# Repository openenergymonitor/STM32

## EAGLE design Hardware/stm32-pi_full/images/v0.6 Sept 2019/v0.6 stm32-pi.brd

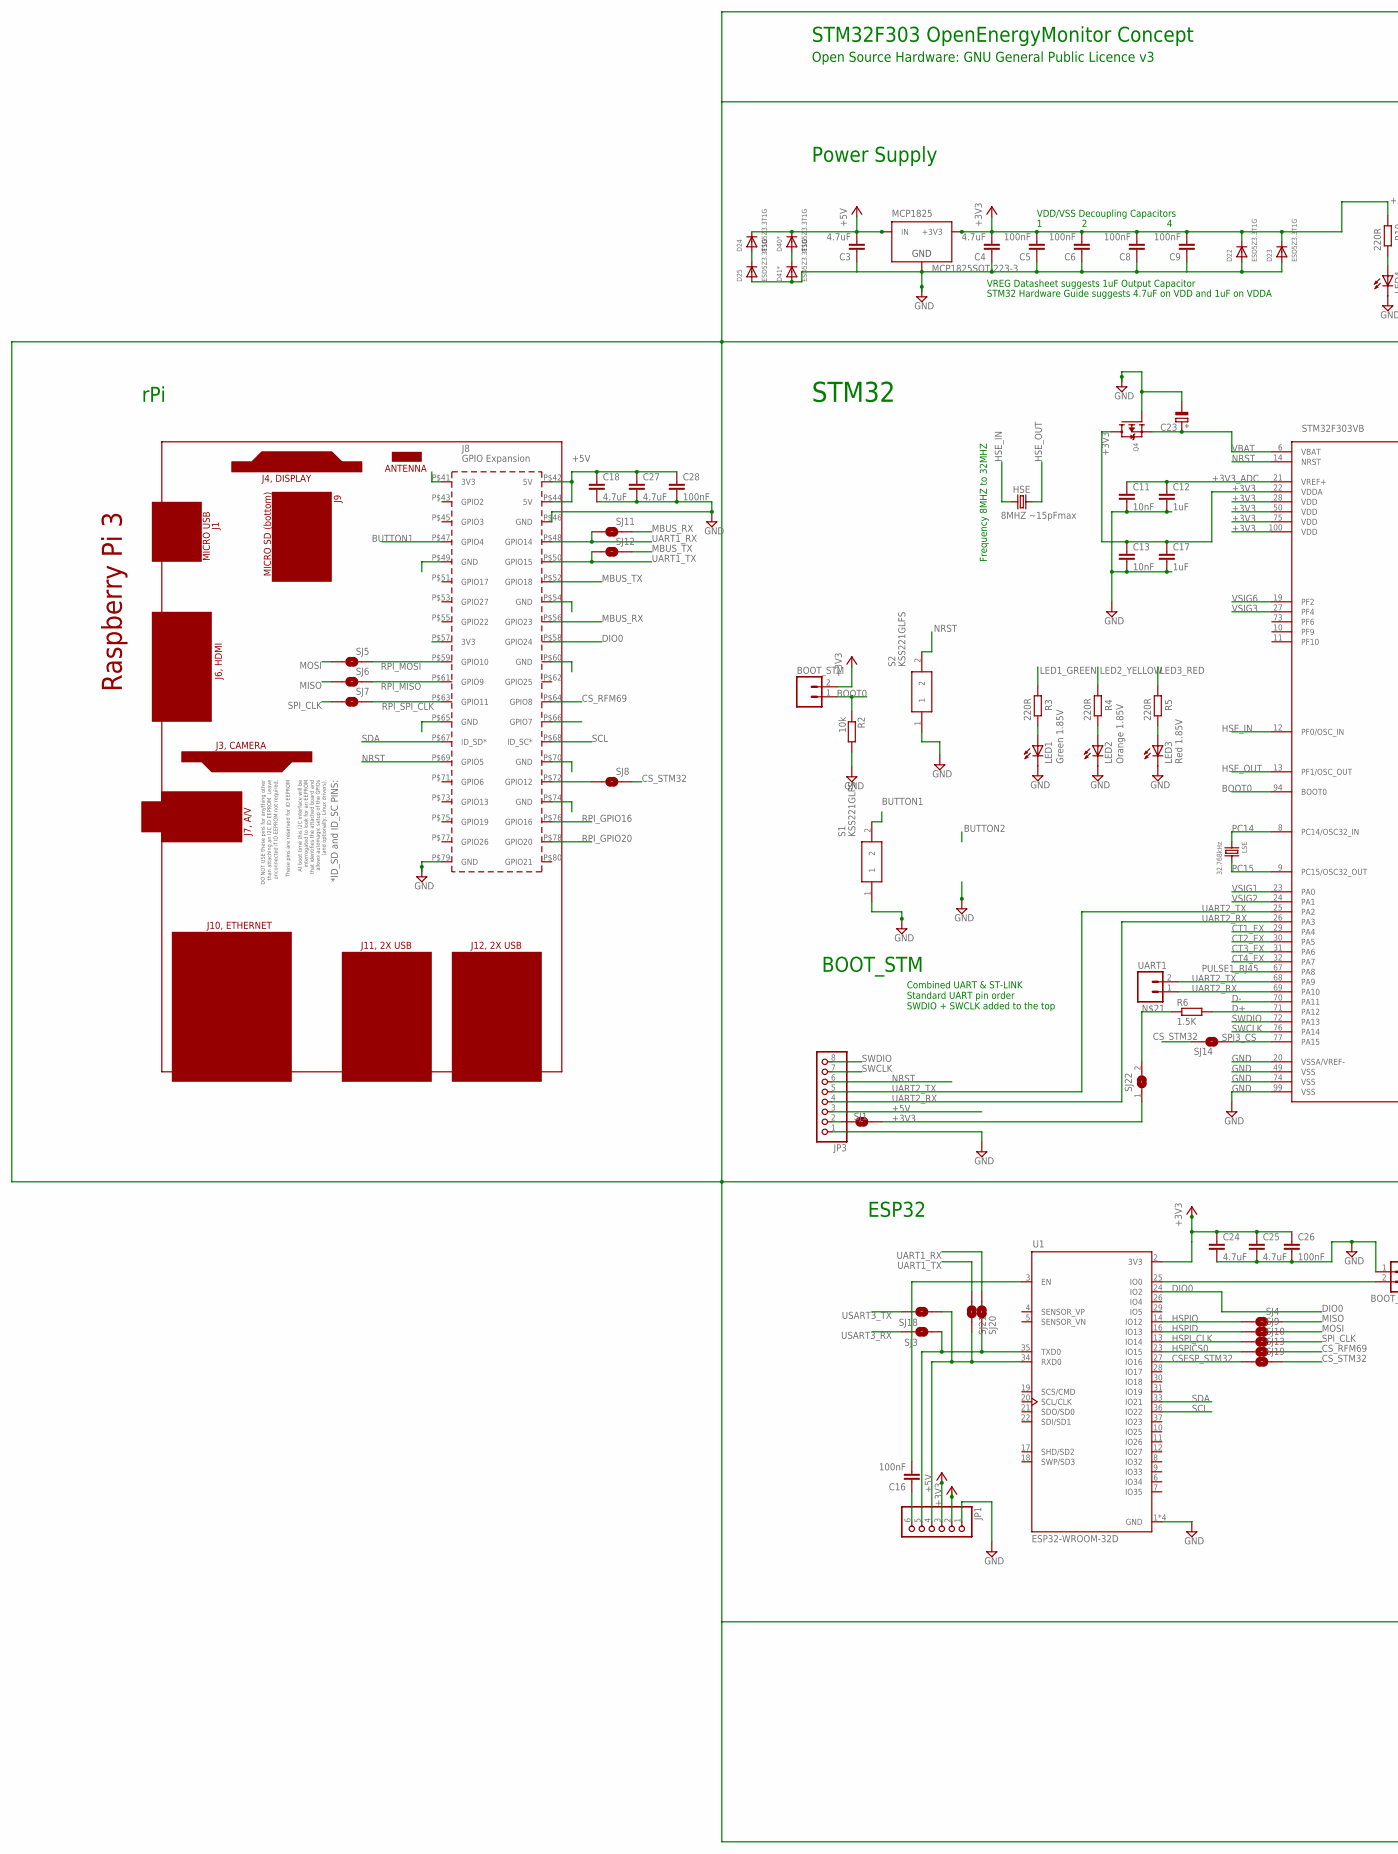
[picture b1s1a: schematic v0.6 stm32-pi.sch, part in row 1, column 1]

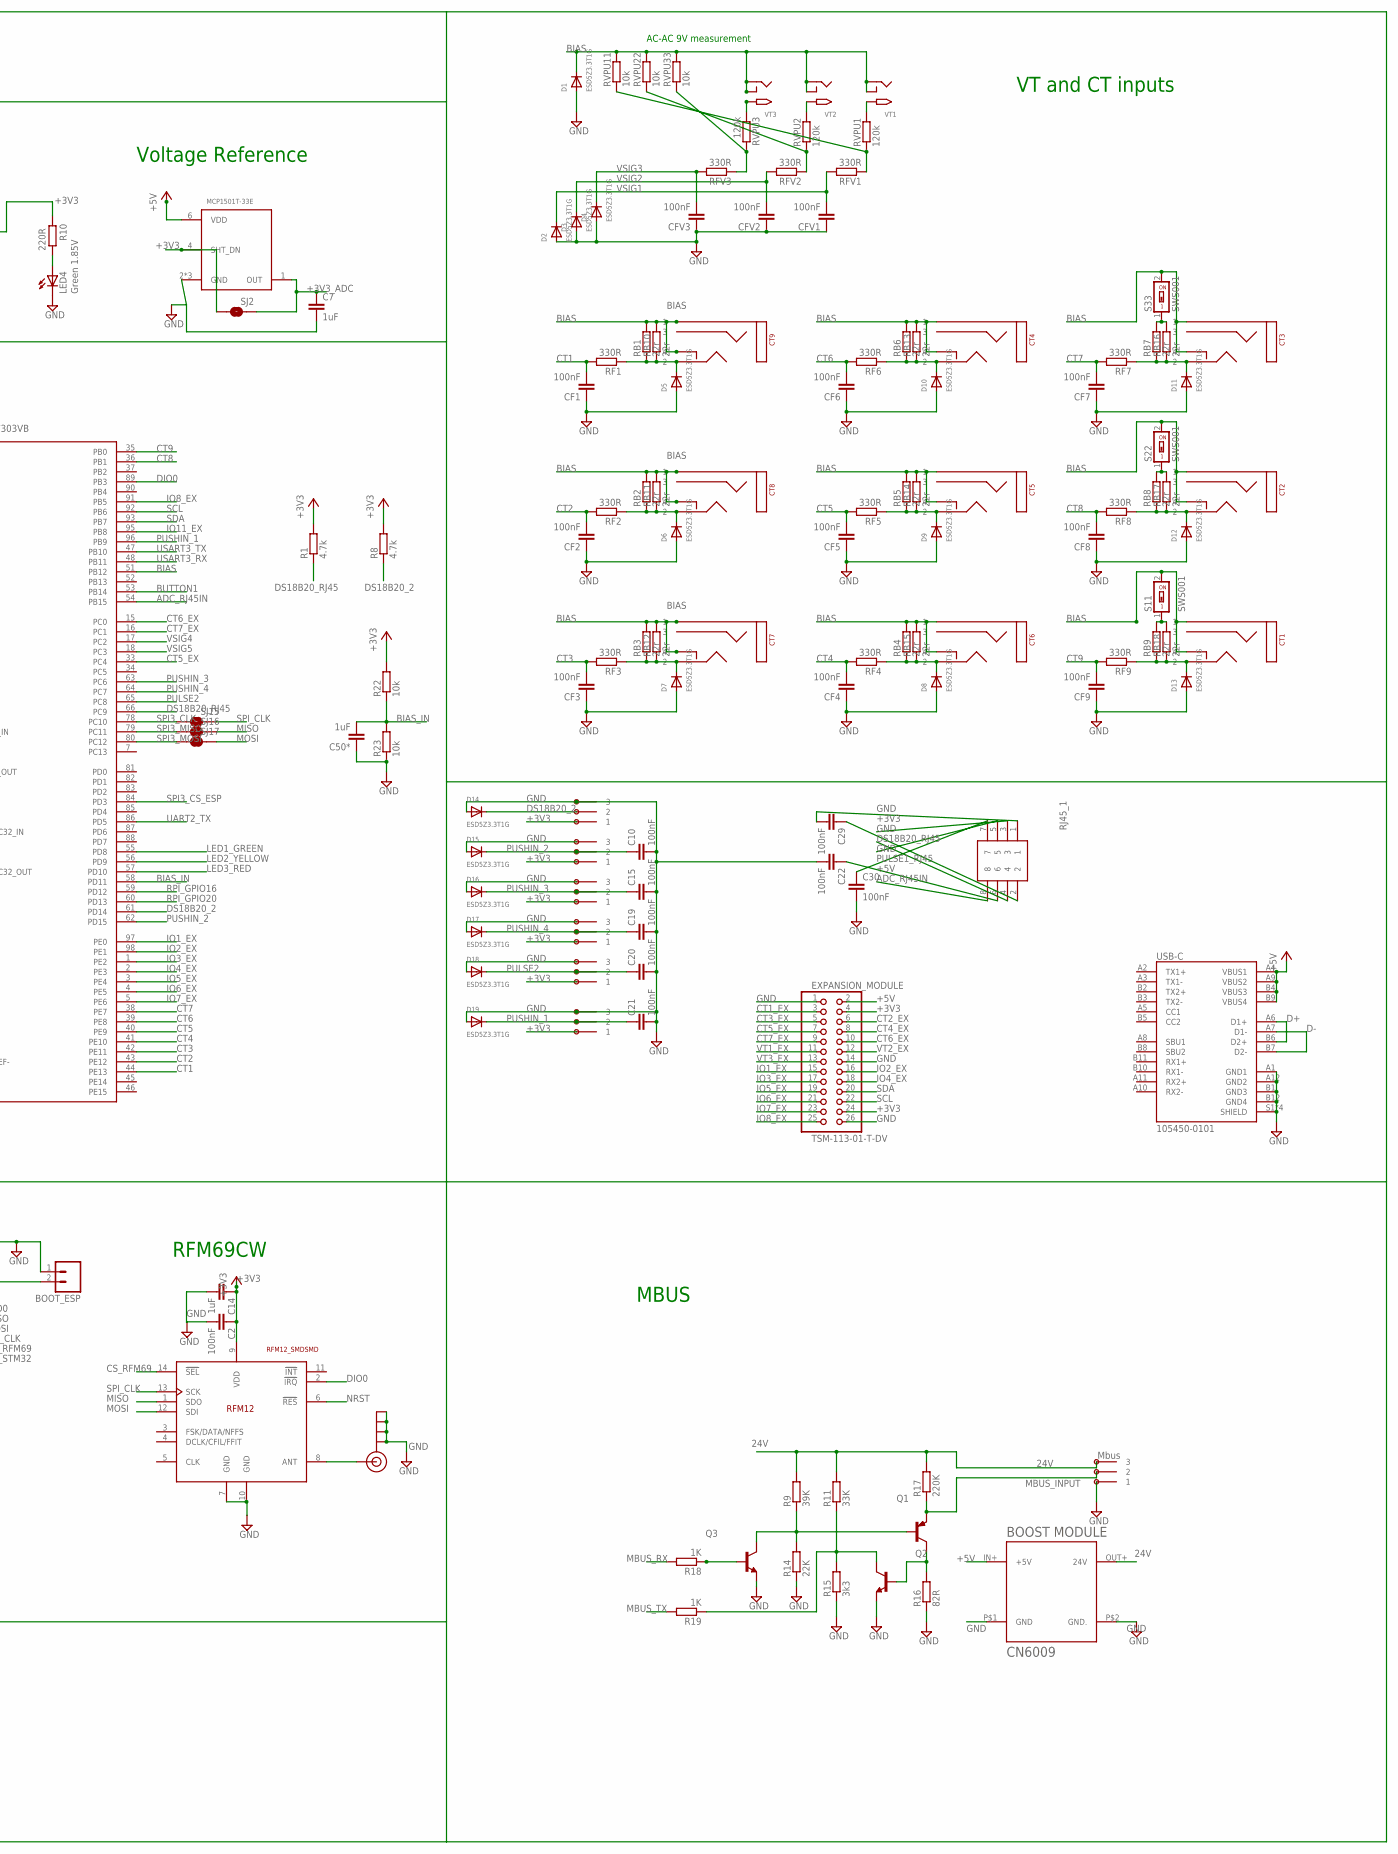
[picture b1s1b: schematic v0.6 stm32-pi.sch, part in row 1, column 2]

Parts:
3POLE_1, 3POLE_2, 3POLE_3, 3POLE_4, 3POLE_5, 3POLE_6, 3POLE_7: OMNIMATE_LSF_3COMBICON_SMT_3; OMNIMATE_LSF_3_SMT
BOOT_ESP: M02PTH; 1X02
BOOT_STM: M02PTH; 1X02
C2, C5, C6, C8, C9, C10, C15, C16, C19, C20, C21, C22, C26, C28, C29, C30: 100nF; C0603
C3, C4, C18, C24, C25, C27: 4.7uF; C0805
C7, C12, C14, C17: 1uF; C0805
C11, C13: 10nF; C0603
C23: CPOL-EU153CLV-1010; 153CLV-1010
C50*: 1uF; C0603
CF1, CF2, CF3, CF4, CF5, CF6, CF7, CF8, CF9: 100nF; C0603
CFV1, CFV2, CFV3: 100nF; C0603
CT1, CT2, CT3, CT4, CT5, CT6, CT7, CT8, CT9: STEREO_SMD; STEREO_SMT
D1, D2, D3, D4, D5, D6, D7, D8, D9, D10, D11, D12, D13, D14, D15, D16, D17, D18, D19, D22, D23, D24, D25, D40*, D41*: ESD5Z3.3T1G; SOD-523
EXPANSION_MODULE: TSM-113-01-T-DV; 2X13_SMT
HSE: 8MHZ ~15pFmax; CTS406
J$1: SMA_EDGE; SMA-EDGE
JP1: PINHD-1X61X06_SMT; 1X06_SMT
JP3: PINHD-1X81X08_SMT; 1X08_SMT
LED1, LED4: Green 1.85V; CHIP-LED0805
LED2: Orange 1.85V; CHIP-LED0805
LED3: Red 1.85V; CHIP-LED0805
LSE: 32.768kHz; CRYSTAL_8X3.8
MCP1825: MCP1825SOT-223-3; SOT-223
PCB2: RPI3YA; RPI3MIRROR2
Q1: MMBT3906; SOT23
Q2, Q3: MMBT3904; SOT23
Q4: MOSFET-P; SOT23-R
R1, R8: 4.7k; R0603
R2, R22, R23: 10k; R0603
R3, R4, R5, R10: 220R; R0603
R6: 1.5K; R0603
R9: 39K; R0603
R11: 33K; R0603
R14: 22K; R0603
R15: 3k3; R0603
R16: 82R; R0603
R17: 220K; R0603
R18, R19: 1K; R0603
RB1, RB2, RB3, RB4, RB5, RB6, RB7, RB8, RB9: 22r; R0603
RB10, RB11, RB12, RB13, RB14, RB15, RB16, RB17, RB18: 22r; 0207/7
RF1, RF2, RF3, RF4, RF5, RF6, RF7, RF8, RF9: 330R; R0603
RFM69HCW: RFM12_SMDSMD; RFM12
RFV1, RFV2, RFV3: 330R; R0603
RJ45_1: 95501-6889; 955016889
RVPU1, RVPU2, RVPU3: 120k; R0603
RVPU11, RVPU22, RVPU33: 10k; R0603
S1, S2: KSS221GLFS; KSS
S11, S22, S33: SWS001; SMS-001
SJ1, SJ2, SJ3, SJ4, SJ5, SJ6, SJ7, SJ8, SJ9, SJ10, SJ11, SJ12, SJ13, SJ14, SJ15, SJ16, SJ17, SJ18, SJ19, SJ20, SJ21: SOLDERJUMPERNO; SJ_2S-NO
SJ22: SJ-CONCON; SJ-CON
STM32F303VB: STM32F303XB; TQFP100
U1: ESP32-WROOM-32D; MODULE_ESP32-WROOM-32D
U$2: BOOST_MODULE; BOOST
UART1: M02PTH; 1X02
USB-C: 105450-0101; MOLEX_105450-0101
VREF_3V3: MCP1501T-33E; SOT95P280X145-6N
VT1, VT2, VT3: 2.1MMJACKSMT; DCJACK_2MM_SMT

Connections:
24V: 3POLE_7.P$3 (3), R9.2, R11.2, R17.2, U$2.OUT+ (24V)
+3V3: 3POLE_1.P$1 (1), 3POLE_2.P$1 (1), 3POLE_3.P$1 (1), 3POLE_4.P$1 (1), 3POLE_5.P$1 (1), 3POLE_6.P$1 (1), BOOT_STM.2, C2.1, C4.2, C5.2, C6.2, C8.2, C9.2, C13.1, C14.1, C17.1, C24.1, C25.1, C26.1, C29.1, D22.K (C), D23.K (C), EXPANSION_MODULE.4, EXPANSION_MODULE.24, JP1.2, MCP1825.3 (+3V3), Q4.3 (D), R1.2, R8.2, R10.2, R22.2, RFM69HCW.9 (VDD), RJ45_1.2, SJ1.2, SJ2.1, SJ22.1, STM32F303VB.22 (VDDA), STM32F303VB.28 (VDD), STM32F303VB.50 (VDD), STM32F303VB.75 (VDD), STM32F303VB.100 (VDD), U1.2 (3V3), VREF_3V3.4 (SHT_DN)
+3V3_ADC: C7.1, C11.1, C12.1, SJ2.2, STM32F303VB.21 (VREF+), VREF_3V3.1 (OUT)
+5V: C3.2, C18.1, C27.1, C28.1, C30.1, D24.K (C), D40*.K (C), EXPANSION_MODULE.2, JP1.3, JP3.3, MCP1825.1 (IN), PCB2.P$42 (5V), PCB2.P$44 (5V), RJ45_1.7, U$2.IN+ (+5V), USB-C.A4 (VBUS1), USB-C.A9 (VBUS2), USB-C.B4 (VBUS3), USB-C.B9 (VBUS4), VREF_3V3.6 (VDD)
AC1: RVPU1.2, VT1.PWR2 (TIP)
AC2: RVPU2.2, VT2.PWR2 (TIP)
AC3: RVPU3.1, VT3.PWR2 (TIP)
ADC0: RFV3.1, RVPU3.2, RVPU33.1
ADC_RJ45IN: RJ45_1.8, STM32F303VB.54 (PB15)
BIAS: CT1.P$1 (1), CT1.P$4 (4), CT2.P$1 (1), CT2.P$4 (4), CT3.P$1 (1), CT3.P$4 (4), CT4.P$1 (1), CT4.P$4 (4), CT5.P$1 (1), CT5.P$4 (4), CT6.P$1 (1), CT6.P$4 (4), CT7.P$1 (1), CT7.P$4 (4), CT8.P$1 (1), CT8.P$4 (4), CT9.P$1 (1), CT9.P$4 (4), D1.K (C), RB1.2, RB2.2, RB3.2, RB4.2, RB5.2, RB6.2, RB10.2, RB11.2, RB12.2, RB13.2, RB14.2, RB15.2, RVPU11.2, RVPU22.2, RVPU33.2, S11.2, S22.2, S33.2, STM32F303VB.51 (PB12), VT1.GND (RING), VT1.GNDBREAK (RING_SW), VT2.GND (RING), VT2.GNDBREAK (RING_SW), VT3.GND (RING), VT3.GNDBREAK (RING_SW)
BIAS_IN: C50*.2, R22.1, R23.2, STM32F303VB.58 (PD11)
BOOT0: BOOT_STM.1, R2.1, STM32F303VB.94 (BOOT0)
BUTTON1: PCB2.P$47 (GPIO4), S1.2, STM32F303VB.53 (PB14)
CSESP_STM32: SJ19.1, U1.27 (IO16)
CS_RFM69: PCB2.P$64 (GPIO8), RFM69HCW.14 (!SEL), SJ13.2
CS_STM32: SJ8.2, SJ14.1, SJ19.2
CT1: CF1.2, RF1.2, STM32F303VB.44 (PE13)
CT1_EX: EXPANSION_MODULE.3, STM32F303VB.29 (PA4)
CT2: CF2.2, RF2.2, STM32F303VB.43 (PE12)
CT2_EX: EXPANSION_MODULE.6, STM32F303VB.30 (PA5)
CT3: CF3.2, RF3.2, STM32F303VB.42 (PE11)
CT3_EX: EXPANSION_MODULE.5, STM32F303VB.31 (PA6)
CT4: CF4.2, RF4.2, STM32F303VB.41 (PE10)
CT4_EX: EXPANSION_MODULE.8, STM32F303VB.32 (PA7)
CT5: CF5.2, RF5.2, STM32F303VB.40 (PE9)
CT5_EX: EXPANSION_MODULE.7, STM32F303VB.33 (PC4)
CT6: CF6.2, RF6.2, STM32F303VB.39 (PE8)
CT6_EX: EXPANSION_MODULE.10, STM32F303VB.15 (PC0)
CT7: CF7.2, RF7.2, STM32F303VB.38 (PE7)
CT7_EX: EXPANSION_MODULE.9, STM32F303VB.16 (PC1)
CT8: CF8.2, RF8.2, STM32F303VB.36 (PB1)
CT9: CF9.2, RF9.2, STM32F303VB.35 (PB0)
D+: R6.2, STM32F303VB.71 (PA12), USB-C.A6 (D1+), USB-C.B6 (D2+)
D-: STM32F303VB.70 (PA11), USB-C.A7 (D1-), USB-C.B7 (D2-)
DIO0: PCB2.P$58 (GPIO24), RFM69HCW.2 (!IRQ), STM32F303VB.89 (PB3), U1.24 (IO2)
DS18B20_2: 3POLE_1.P$2 (2), D14.K (C), R8.1, STM32F303VB.61 (PD14)
DS18B20_RJ45: R1.1, RJ45_1.4, STM32F303VB.66 (PC9)
GND: 3POLE_1.P$3 (3), 3POLE_2.P$3 (3), 3POLE_3.P$3 (3), 3POLE_4.P$3 (3), 3POLE_5.P$3 (3), 3POLE_6.P$3 (3), 3POLE_7.P$1 (1), BOOT_ESP.1, C2.2, C3.1, C4.1, C5.1, C6.1, C7.2, C8.1, C9.1, C10.2, C11.2, C12.2, C13.2, C14.2, C15.2, C17.2, C18.2, C19.2, C20.2, C21.2, C22.2, C23.-, C24.2, C25.2, C26.2, C27.2, C28.2, C29.2, C30.2, C50*.1, CF1.1, CF2.1, CF3.1, CF4.1, CF5.1, CF6.1, CF7.1, CF8.1, CF9.1, CFV1.1, CFV2.1, CFV3.1, D1.A, D2.A, D3.A, D4.A, D5.A, D6.A, D7.A, D8.A, D9.A, D10.A, D11.A, D12.A, D13.A, D14.A, D15.A, D16.A, D17.A, D18.A, D19.A, D22.A, D23.A, D25.A, D41*.A, EXPANSION_MODULE.1, EXPANSION_MODULE.14, EXPANSION_MODULE.26, J$1.GND@0 (GND), J$1.GND@1 (GND), J$1.GND@2 (GND), J$1.GND@3 (GND), JP1.1, JP3.1, LED1.C, LED2.C, LED3.C, LED4.C, MCP1825.2 (GND), MCP1825.4 (GND), PCB2.P$46 (GND), PCB2.P$49 (GND), PCB2.P$54 (GND), PCB2.P$60 (GND), PCB2.P$65 (GND), PCB2.P$70 (GND), PCB2.P$74 (GND), PCB2.P$79 (GND), Q2.2 (E), Q3.2 (E), Q4.1 (G), R2.2, R14.1, R15.1, R16.1, R23.1, RFM69HCW.7 (GND), RFM69HCW.10 (GND), RJ45_1.1, RJ45_1.3, RJ45_1.5, S1.1, S2.1, STM32F303VB.20 (VSSA/VREF-), STM32F303VB.49 (VSS), STM32F303VB.74 (VSS), STM32F303VB.99 (VSS), U1.1 (GND), U1.15 (GND), U1.38 (GND), U1.39 (GND), U$2.P$1 (GND), U$2.P$2 (GND.), USB-C.A1 (GND1), USB-C.A12 (GND2), USB-C.B1 (GND3), USB-C.B12 (GND4), USB-C.S1 (SHIELD), USB-C.S2 (SHIELD), USB-C.S3 (SHIELD), USB-C.S4 (SHIELD), VREF_3V3.2 (GND), VREF_3V3.3 (GND), VREF_3V3.5 (GND)
HSE_IN: HSE.1, STM32F303VB.12 (PF0/OSC_IN)
HSE_OUT: HSE.3 (2), STM32F303VB.13 (PF1/OSC_OUT)
HSPICS0: SJ13.1, U1.23 (IO15)
HSPID: SJ9.1, U1.16 (IO13)
HSPIQ: SJ4.1, U1.14 (IO12)
HSPI_CLK: SJ10.1, U1.13 (IO14)
IO1_EX: EXPANSION_MODULE.15, STM32F303VB.97 (PE0)
IO2_EX: EXPANSION_MODULE.16, STM32F303VB.98 (PE1)
IO3_EX: EXPANSION_MODULE.17, STM32F303VB.1 (PE2)
IO4_EX: EXPANSION_MODULE.18, STM32F303VB.2 (PE3)
IO5_EX: EXPANSION_MODULE.19, STM32F303VB.3 (PE4)
IO6_EX: EXPANSION_MODULE.21, STM32F303VB.4 (PE5)
IO7_EX: EXPANSION_MODULE.23, STM32F303VB.5 (PE6)
IO8_EX: EXPANSION_MODULE.25, STM32F303VB.91 (PB5)
IO11_EX: STM32F303VB.95 (PB8)
LED1_GREEN: R3.2, STM32F303VB.55 (PD8)
LED2_YELLOW: R4.2, STM32F303VB.56 (PD9)
LED3_RED: R5.2, STM32F303VB.57 (PD10)
MBUS_INPUT: 3POLE_7.P$2 (2), Q1.2 (E), R17.1
MBUS_RX: PCB2.P$56 (GPIO23), R18.2, SJ11.2
MBUS_TX: PCB2.P$52 (GPIO18), R19.2, SJ12.2
MISO: RFM69HCW.1 (SDO), SJ4.2, SJ6.1, SJ16.2
MOSI: RFM69HCW.12 (SDI), SJ5.1, SJ9.2, SJ17.2
unnamed: JP3.2, SJ1.1
unnamed: CT9.P$2 (2), D5.K (C), RB1.1, RB10.1, RF1.1
unnamed: LED2.A, R4.1
unnamed: LED3.A, R5.1
unnamed: JP1.5, SJ3.1, SJ20.2, U1.35 (TXD0)
unnamed: CT8.P$2 (2), D6.K (C), RB2.1, RB11.1, RF2.1
unnamed: LED4.A, R10.1
unnamed: CT7.P$2 (2), D7.K (C), RB3.1, RB12.1, RF3.1
unnamed: JP1.4, SJ18.1, SJ21.2, U1.34 (RXD0)
unnamed: STM32F303VB.68 (PA9), UART1.2
unnamed: C16.1, JP1.6
unnamed: C16.2, U1.3 (EN)
unnamed: PCB2.P$72 (GPIO12), SJ8.1
unnamed: BOOT_ESP.2, U1.25 (IO0)
unnamed: D24.A, D25.K (C)
unnamed: D40*.A, D41*.K (C)
unnamed: J$1.SIG (SIGNAL), RFM69HCW.8 (ANT)
unnamed: R6.1, SJ22.2
unnamed: STM32F303VB.69 (PA10), UART1.1
unnamed: RB9.2, RB18.2, S11.1
unnamed: RB8.2, RB17.2, S22.1
unnamed: RB7.2, RB16.2, S33.1
unnamed: Q1.3 (C), Q2.1 (B), R16.2
unnamed: Q1.1 (B), Q3.3 (C), R9.1, R14.2
unnamed: Q2.3 (C), R11.1, R15.2, R19.1
unnamed: Q3.1 (B), R18.1
unnamed: RFV2.1, RVPU2.1, RVPU22.1
unnamed: RFV1.1, RVPU1.1, RVPU11.1
unnamed: CT6.P$2 (2), D8.K (C), RB4.1, RB15.1, RF4.1
unnamed: CT5.P$2 (2), D9.K (C), RB5.1, RB14.1, RF5.1
unnamed: CT4.P$2 (2), D10.K (C), RB6.1, RB13.1, RF6.1
unnamed: LED1.A, R3.1
unnamed: CT3.P$2 (2), D11.K (C), RB7.1, RB16.1, RF7.1
unnamed: CT2.P$2 (2), D12.K (C), RB8.1, RB17.1, RF8.1
unnamed: CT1.P$2 (2), D13.K (C), RB9.1, RB18.1, RF9.1
NRST: JP3.6, PCB2.P$69 (GPIO5), RFM69HCW.6 (!RES), S2.2, STM32F303VB.14 (NRST)
PC14: LSE.P$1 (1), STM32F303VB.8 (PC14/OSC32_IN)
PC15: LSE.P$4 (2), STM32F303VB.9 (PC15/OSC32_OUT)
PULSE1_RJ45: C22.1, RJ45_1.6, STM32F303VB.67 (PA8)
PULSE2: 3POLE_5.P$2 (2), C20.1, D18.K (C), STM32F303VB.65 (PC8)
PUSHIN_1: 3POLE_6.P$2 (2), C21.1, D19.K (C), STM32F303VB.96 (PB9)
PUSHIN_2: 3POLE_2.P$2 (2), C10.1, D15.K (C), STM32F303VB.62 (PD15)
PUSHIN_3: 3POLE_3.P$2 (2), C15.1, D16.K (C), STM32F303VB.63 (PC6)
PUSHIN_4: 3POLE_4.P$2 (2), C19.1, D17.K (C), STM32F303VB.64 (PC7)
RPI_GPIO16: PCB2.P$76 (GPIO16), STM32F303VB.59 (PD12)
RPI_GPIO20: PCB2.P$78 (GPIO20), STM32F303VB.60 (PD13)
RPI_MISO: PCB2.P$61 (GPIO9), SJ6.2
RPI_MOSI: PCB2.P$59 (GPIO10), SJ5.2
RPI_SPI_CLK: PCB2.P$63 (GPIO11), SJ7.2
SCL: EXPANSION_MODULE.22, PCB2.P$68 (ID_SC*), STM32F303VB.92 (PB6), U1.36 (IO22)
SDA: EXPANSION_MODULE.20, PCB2.P$67 (ID_SD*), STM32F303VB.93 (PB7), U1.33 (IO21)
SPI3_CLK: SJ15.1, STM32F303VB.78 (PC10)
SPI3_CS: SJ14.2, STM32F303VB.77 (PA15)
SPI3_CS_ESP: STM32F303VB.84 (PD3)
SPI3_MISO: SJ16.1, STM32F303VB.79 (PC11)
SPI3_MOSI: SJ17.1, STM32F303VB.80 (PC12)
SPI_CLK: RFM69HCW.13 (SCK), SJ7.1, SJ10.2, SJ15.2
SWCLK: JP3.7, STM32F303VB.76 (PA14)
SWDIO: JP3.8, STM32F303VB.72 (PA13)
UART1_RX: PCB2.P$48 (GPIO14), SJ11.1, SJ20.1
UART1_TX: PCB2.P$50 (GPIO15), SJ12.1, SJ21.1
UART2_RX: JP3.4, STM32F303VB.26 (PA3)
UART2_TX: JP3.5, STM32F303VB.25 (PA2), STM32F303VB.86 (PD5)
USART3_RX: SJ3.2, STM32F303VB.48 (PB11)
USART3_TX: SJ18.2, STM32F303VB.47 (PB10)
VBAT: C23.+, Q4.2 (S), STM32F303VB.6 (VBAT)
VSIG1: CFV1.2, D2.K (C), RFV1.2, STM32F303VB.23 (PA0)
VSIG2: CFV2.2, D3.K (C), RFV2.2, STM32F303VB.24 (PA1)
VSIG3: CFV3.2, D4.K (C), RFV3.2, STM32F303VB.27 (PF4)
VSIG4: STM32F303VB.17 (PC2)
VSIG5: STM32F303VB.18 (PC3)
VSIG6: STM32F303VB.19 (PF2)
VT1_EX: EXPANSION_MODULE.11
VT2_EX: EXPANSION_MODULE.12
VT3_EX: EXPANSION_MODULE.13

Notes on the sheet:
VDD/VSS Decoupling Capacitors
VREG Datasheet suggests 1uF Output Capacitor
STM32 Hardware Guide suggests 4.7uF on VDD and 1uF on VDDA
Combined UART & ST-LINK Standard UART pin order SWDIO + SWCLK added to the top
AC-AC 9V measurement
VT and CT inputs
STM32F303 OpenEnergyMonitor Concept
Power Supply
STM32
Open Source Hardware: GNU General Public Licence v3
Frequency 8MHZ to 32MHZ
Mbus
Voltage Reference
ESP32
MBUS
rPi
BOOT_STM
RFM69CW

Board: 2 copper layers, 194 parts (8 on the bottom side), 128 nets, no tracks yet.

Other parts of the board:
LOGO1: OSHW_LOGO_6MILX0200-NT; OSHW_6X200_NOTEXT

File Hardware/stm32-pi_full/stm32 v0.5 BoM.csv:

Qty,Value,Package,Schematic Reference,Description,CREATED_BY,DIGIKEY_PART_NUMBER,MANUFACTURER,MF,MPN,OC_FARNELL,OC_NEWARK,PACKAGE,PROD_ID,SF_ID,SPICEPREFIX,VALUE
2,,B3F-31XX,"BUTTON1, RST",OMRON SWITCH,,,,,B3F-3100,959704,36M3582,,,,,
1,,ESP12-SMD,ESP12,ESP8266 Wifi module 12,,,,,,,,,,,,
3,,1X02,"BOOT_ESP, BOOT_STM, UART1",Header 2,,,,,,,,,,,,
1,,1X03,STLINK,Header 3,,,,,,,,,,,,
2,,MA06-1,"UART_ESP, UART_STM",PIN HEADER,,,,,,unknown,unknown,,,,,
1,,MA13-2,EXPANSION_MODULE,PIN HEADER,,,,,,unknown,unknown,,,,,
25,100nF,C0603,"C1, C2, C5, C6, C8, C9, C10, C15, C19, C20, C21, C22, C23, CF1, CF2, CF3, CF4, CF5, CF6, CF7, CF8, CF9, CFV1, CFV2, CFV3","CAPACITOR, European symbol",,,,,,,,,,,,
8,10k,R0603,"R2, R6, R7, R22, R23, RVPU11, RVPU22, RVPU33","RESISTOR, European symbol",,,,,,,,,,,,
2,10nF,C0603,"C11, C13","CAPACITOR, European symbol",,,,,,,,,,,C,
1,10uF,C0603,C18,"CAPACITOR, European symbol",,,,,,,,,,,,
3,120k,R0603,"RVPU1, RVPU2, RVPU3","RESISTOR, European symbol",,,,,,,,,,,,
2,1K,R0603,"R18, R19","RESISTOR, European symbol",,,,,,,,,,,R,
2,1uF,C0603,"C12, C17","CAPACITOR, European symbol",,,,,,,,,,,,
2,1uF,C0805,"C7, C14","CAPACITOR, European symbol",,,,,,,,,,,C,
3,2.1MMJACKSMT,DCJACK_2MM_SMT,"VT1, VT2, VT3","2.1mm x 5.5mm THM DC jack with internal switch. Digikey part #PJ-102A, 4UCON part #05537",,,,,,,,,,,,
1,220K,R0603,R17,"RESISTOR, European symbol",,,,,,,,,,,R,
3,220R,R0603,"R3, R4, R5","RESISTOR, European symbol",,,,,,,,,,,R,
1,22K,R0603,R14,"RESISTOR, European symbol",,,,,,,,,,,R,
9,22r,0207/7,"RB10, RB11, RB12, RB13, RB14, RB15, RB16, RB17, RB18","RESISTOR, European symbol",,,,,,,,,,,R,
9,22r,R0603,"RB1, RB2, RB3, RB4, RB5, RB6, RB7, RB8, RB9","RESISTOR, European symbol",,,,,,,,,,,,
1,32.768kHz,CRYSTAL_8X3.8,Y1,Crystals,,,,,,,,,,,,
12,330R,R0603,"RF1, RF2, RF3, RF4, RF5, RF6, RF7, RF8, RF9, RFV1, RFV2, RFV3","RESISTOR, European symbol",,,,,,,,,,,,
1,33K,R0603,R11,"RESISTOR, European symbol",,,,,,,,,,,R,
1,39K,R0603,R9,"RESISTOR, European symbol",,,,,,,,,,,R,
1,3k3,R0603,R15,"RESISTOR, European symbol",,,,,,,,,,,R,
2,4.7k,R0603,"R1, R8","RESISTOR, European symbol",,,,,,,,,,,,
2,4.7uF,C0805,"C3, C4","CAPACITOR, European symbol",,,,,,,,,,,C,
1,47uF,C0805,C24,"CAPACITOR, European symbol",,,,,,,,,,,C,
1,82R,R0603,R16,"RESISTOR, European symbol",,,,,,,,,,,R,
1,8MHZ ~15pFmax,CTS406,HSE,CRYSTAL,,,,,,unknown,unknown,,,,,
1,BOOST_MODULE,BOOST,U$2,,,,,,,,,,,,,
1,MCP1501T-33E,SOT95P280X145-6N,VREF_3V3,,,,,,,,,,,,,
1,MCP1825SOT-223-3,SOT-223,MCP1825,MCP1825 3.3v LDO Linear Regulator,,,,,,,,,,,,
1,MICRO-USB-RECEPTACLE47589-0001,47589-0001,USB_CONN,MICRO USB RECEPTACLES,,,,,,,,,,,,
2,MMBT3904,SOT23,"Q2, Q3",TRANS NPN 40V 0.2A SOT-23,PCB Layout,MMBT3904FSCT-ND,ON Semiconductor,,MMBT3904,,,SOT-23-3,,,,
1,MMBT3906,SOT23,Q1,TRANS PNP 40V 0.2A SOT-23,PCB Layout,MMBT3906FSCT-ND,ON Semiconductor,,MMBT3906,,,SOT-23,,,,
1,OMNIMATE_LSF_2,OMNIMATE_LSF_2,2POLE_MBUS,,,,,,,,,,,,,
6,OMNIMATE_LSF_3,OMNIMATE_LSF_3,"3POLE_1, 3POLE_2, 3POLE_3, 3POLE_4, 3POLE_5, 3POLE_6",,,,,,,,,,,,,
1,RFM12_SMDSMD,RFM12,RFM69HCW,RFM12 is a low costing ISM band transceiver,,,,,,,,,,,,
1,RJ45,RJ45-8,RJ45_1,RJ45 Jack - 8 pin,,,,,,,,,CONN-08506,PRT-00643,,RJ45
1,RPI3YA,RPI3MIRROR2,PCB2,Device for Raspberry Pi 3 board created by Dave Young for www.element14.com,,,,,,,,,,,,
3,Red 1.85V,CHIP-LED0805,"LED1, LED2, LED3",LED,,,,,,,,,,,,
1,SMA_EDGE,SMA-EDGE,J$1,SMA Antenna Connector,,,,,,,,,,,,
10,SOLDERJUMPERNO,SJ_2S-NO,"SJ1, SJ2, SJ5, SJ6, SJ7, SJ8, SJ9, SJ10, SJ11, SJ12",Solder Jumper,,,,,,,,,,,,
9,STEREO_SMD,STEREO_SMT,"CT1, CT2, CT3, CT4, CT5, CT6, CT7, CT8, CT9",3.5mm Stereo Jack SMT,,,,,SJ-3524-SMT-TR ,,,,,,,
1,STM32F303XB,TQFP100,STM32F303VB STM32F303VD STM32F303VE (flash size),,,,,,STM32F303VBT6TR ,,,,,,,
3,SWS001,SMS-001,"S1, S2, S3",SMD Dip Switch 1 pol.,,,,,,,,,,,,

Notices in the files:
parts and their libraries:
SparkFun-Connectors: Licensing: Creative Commons ShareAlike 4.0 International - https://creativecommons.org/licenses/by-sa/4.0
microbuilder: This work is placed in the public domain, and may be freely used for commercial and non-commercial work with the following conditions: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
